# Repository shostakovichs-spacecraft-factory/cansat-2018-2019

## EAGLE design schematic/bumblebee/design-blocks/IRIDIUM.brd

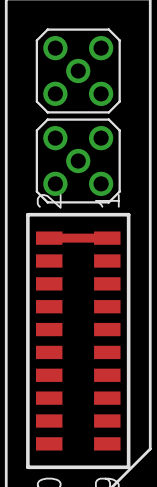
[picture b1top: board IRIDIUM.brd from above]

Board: 2 copper layers, 3 parts (0 on the bottom side), 2 nets.

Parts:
ANT: MMCX-P-P-X-ST-TH1
GPS: MMCX-P-P-X-ST-TH1
USER_PORT: SAMTEC-CLP-110-02-X-DJ; SAMTEC-CLP-110-02-X-D

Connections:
GND: ANT.2, ANT.3, ANT.4, ANT.5, GPS.2, GPS.3, GPS.4, GPS.5, USER_PORT.3, USER_PORT.4, USER_PORT.8, USER_PORT.15, USER_PORT.18
VCC5: USER_PORT.1, USER_PORT.2

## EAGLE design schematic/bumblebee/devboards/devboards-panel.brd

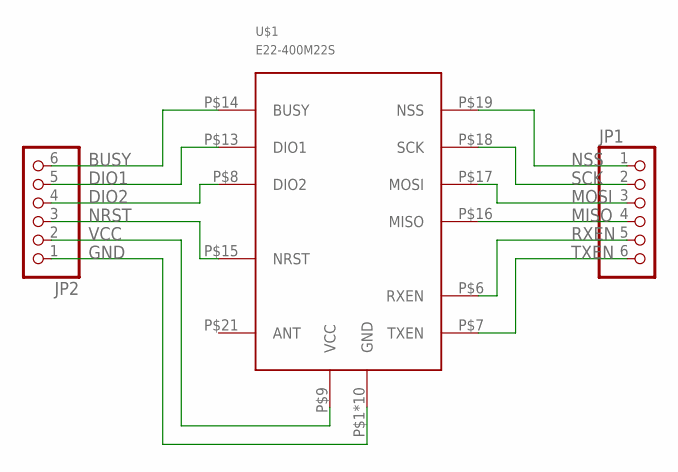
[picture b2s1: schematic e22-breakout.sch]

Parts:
JP1, JP2: PINHD-1X6; 1X06
U$1: E22-400M22S

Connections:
BUSY: JP2.6, U$1.P$14 (BUSY)
DIO1: JP2.5, U$1.P$13 (DIO1)
DIO2: JP2.4, U$1.P$8 (DIO2)
MISO: JP1.4, U$1.P$16 (MISO)
MOSI: JP1.3, U$1.P$17 (MOSI)
NRST: JP2.3, U$1.P$15 (NRST)
NSS: JP1.1, U$1.P$19 (NSS)
RXEN: JP1.5, U$1.P$6 (RXEN)
SCK: JP1.2, U$1.P$18 (SCK)
TXEN: JP1.6, U$1.P$7 (TXEN)
VCC: JP2.2, U$1.P$9 (VCC)

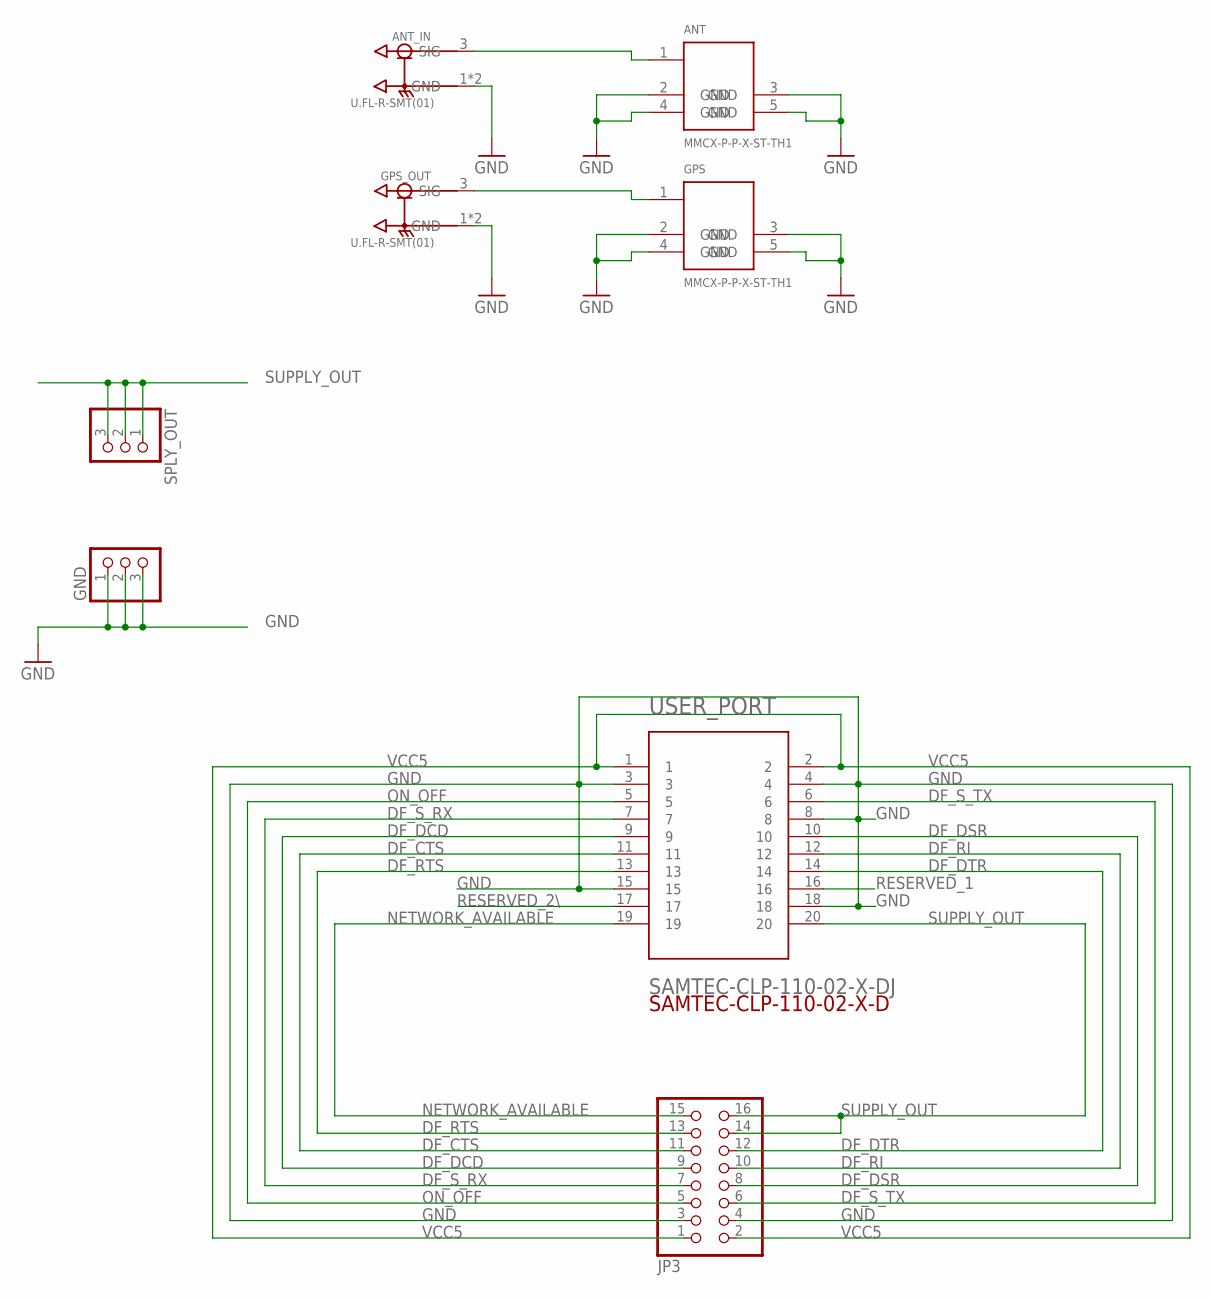
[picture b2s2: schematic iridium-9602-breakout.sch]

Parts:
ANT: MMCX-P-P-X-ST-TH1
ANT_IN: U.FL-R-SMT(01); HRS_U.FL-R-SMT(01)
GND: PINHD-1X3; 1X03
GPS: MMCX-P-P-X-ST-TH1
GPS_OUT: U.FL-R-SMT(01); HRS_U.FL-R-SMT(01)
JP3: PINHD-2X8; 2X08
SPLY_OUT: PINHD-1X3; 1X03
USER_PORT: SAMTEC-CLP-110-02-X-DJ; SAMTEC-CLP-110-02-X-D

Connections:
DF_CTS: JP3.11, USER_PORT.11
DF_DCD: JP3.9, USER_PORT.9
DF_DSR: JP3.8, USER_PORT.10
DF_DTR: JP3.12, USER_PORT.14
DF_RI: JP3.10, USER_PORT.12
DF_RTS: JP3.13, USER_PORT.13
DF_S_RX: JP3.7, USER_PORT.7
DF_S_TX: JP3.6, USER_PORT.6
GND: ANT.2 (GND), ANT.3 (GND), ANT.4 (GND), ANT.5 (GND), ANT_IN.1 (GND), ANT_IN.2 (GND), GND.1, GND.2, GND.3, GPS.2 (GND), GPS.3 (GND), GPS.4 (GND), GPS.5 (GND), GPS_OUT.1 (GND), GPS_OUT.2 (GND), JP3.3, JP3.4, USER_PORT.3, USER_PORT.4, USER_PORT.8, USER_PORT.15, USER_PORT.18
unnamed: ANT.1, ANT_IN.3 (SIG)
unnamed: GPS.1, GPS_OUT.3 (SIG)
NETWORK_AVAILABLE: JP3.15, USER_PORT.19
ON_OFF: JP3.5, USER_PORT.5
RESERVED_1: USER_PORT.16
RESERVED_2\: USER_PORT.17
SUPPLY_OUT: JP3.14, JP3.16, SPLY_OUT.1, SPLY_OUT.2, SPLY_OUT.3, USER_PORT.20
VCC5: JP3.1, JP3.2, USER_PORT.1, USER_PORT.2

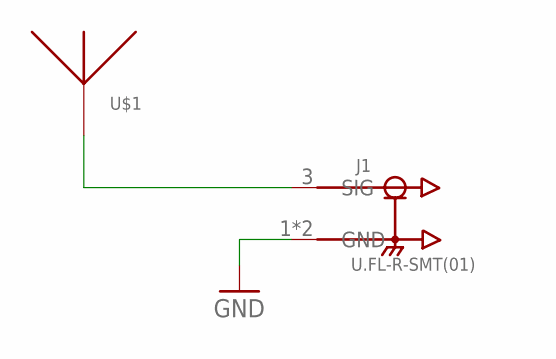
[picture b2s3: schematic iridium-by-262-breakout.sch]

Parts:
J1: U.FL-R-SMT(01); HRS_U.FL-R-SMT(01)
U$1: BY-IRIDIUM-254

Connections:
GND2: J1.1 (GND), J1.2 (GND)

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
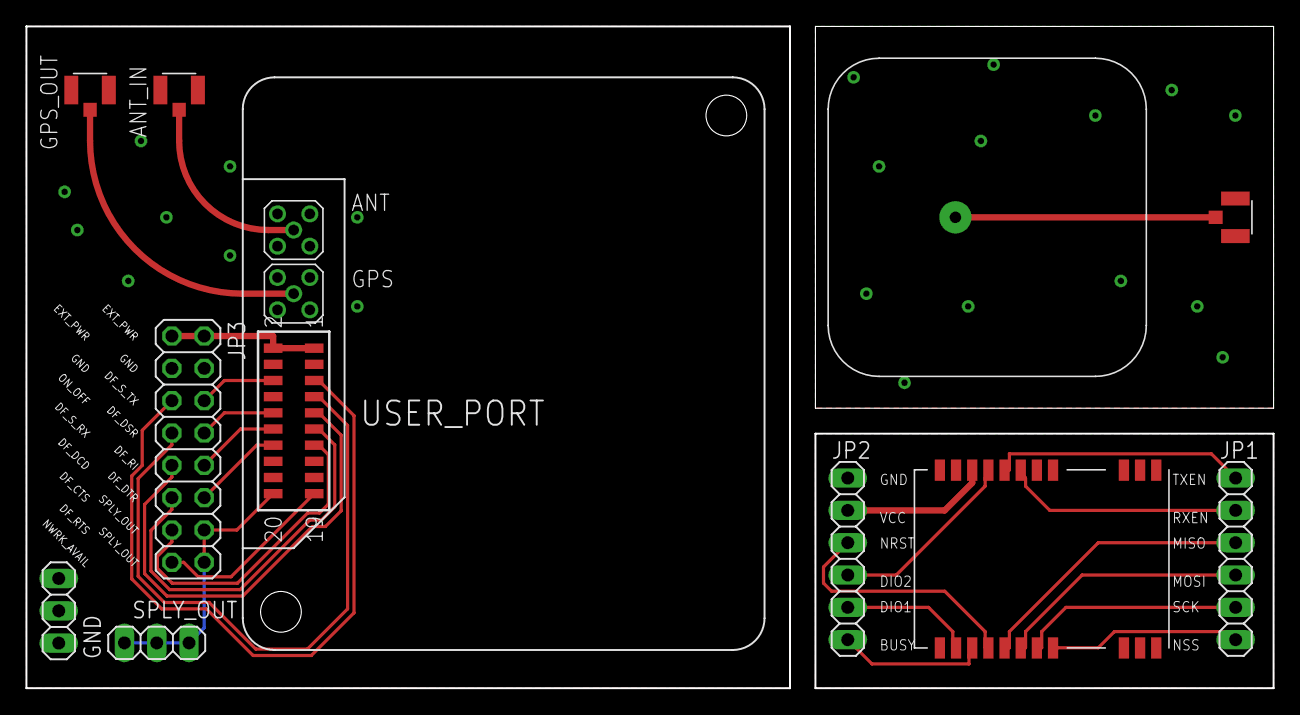
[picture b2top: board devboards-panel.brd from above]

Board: 2 copper layers, 98.0 x 52.0 mm, 13 parts (0 on the bottom side), 29 nets.

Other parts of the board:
U$2: BY-IRIDIUM-254

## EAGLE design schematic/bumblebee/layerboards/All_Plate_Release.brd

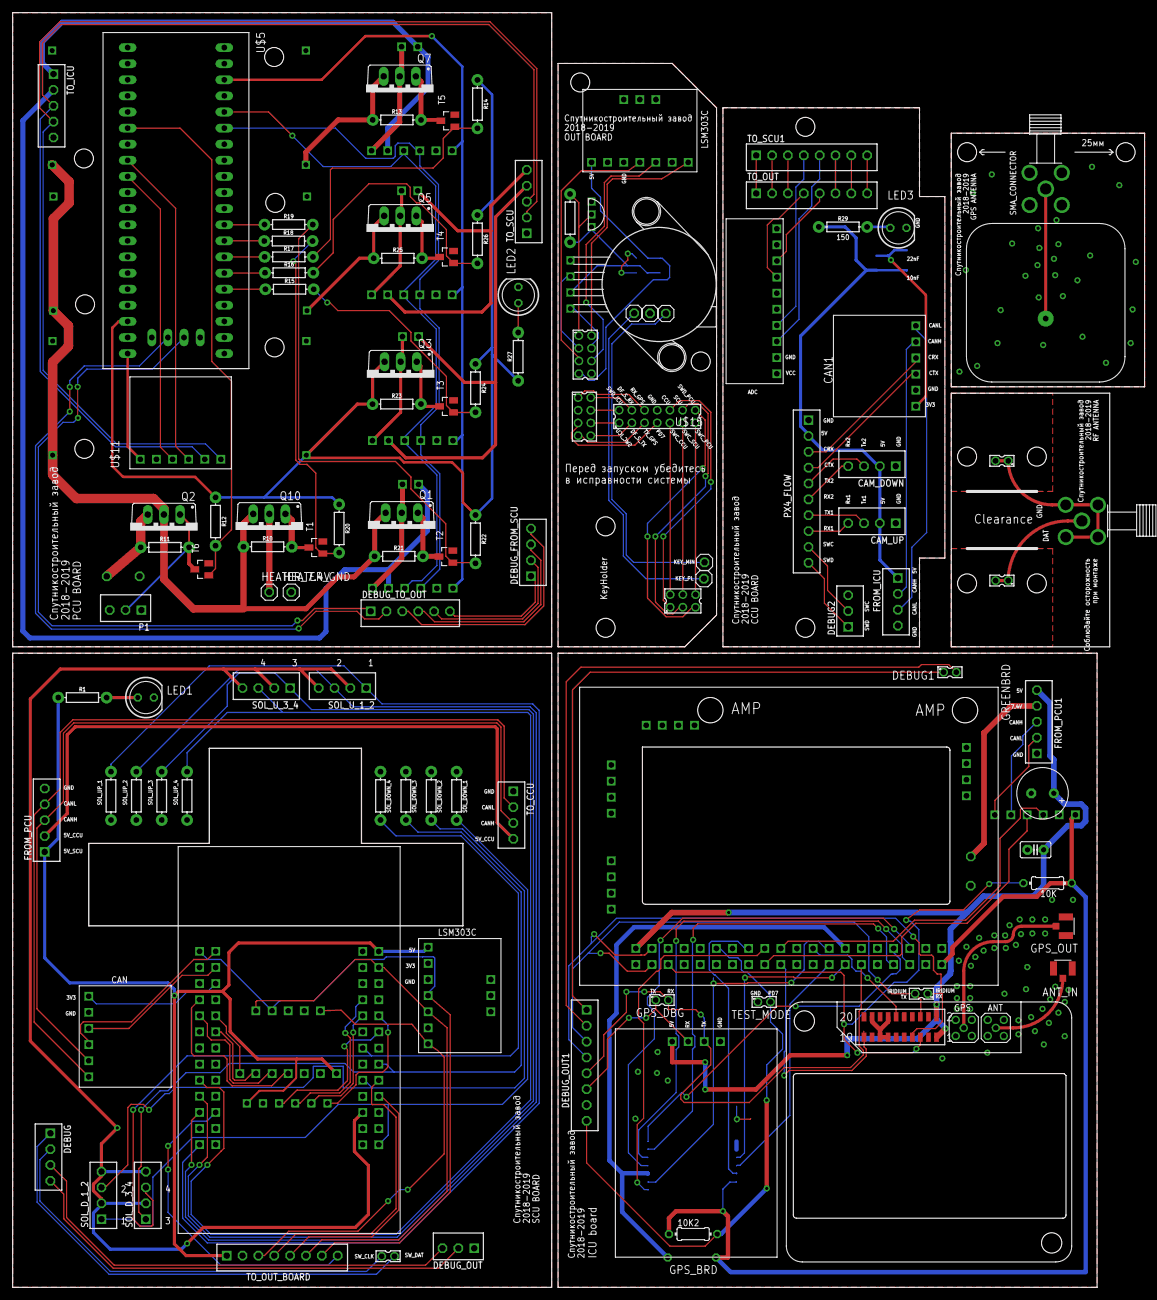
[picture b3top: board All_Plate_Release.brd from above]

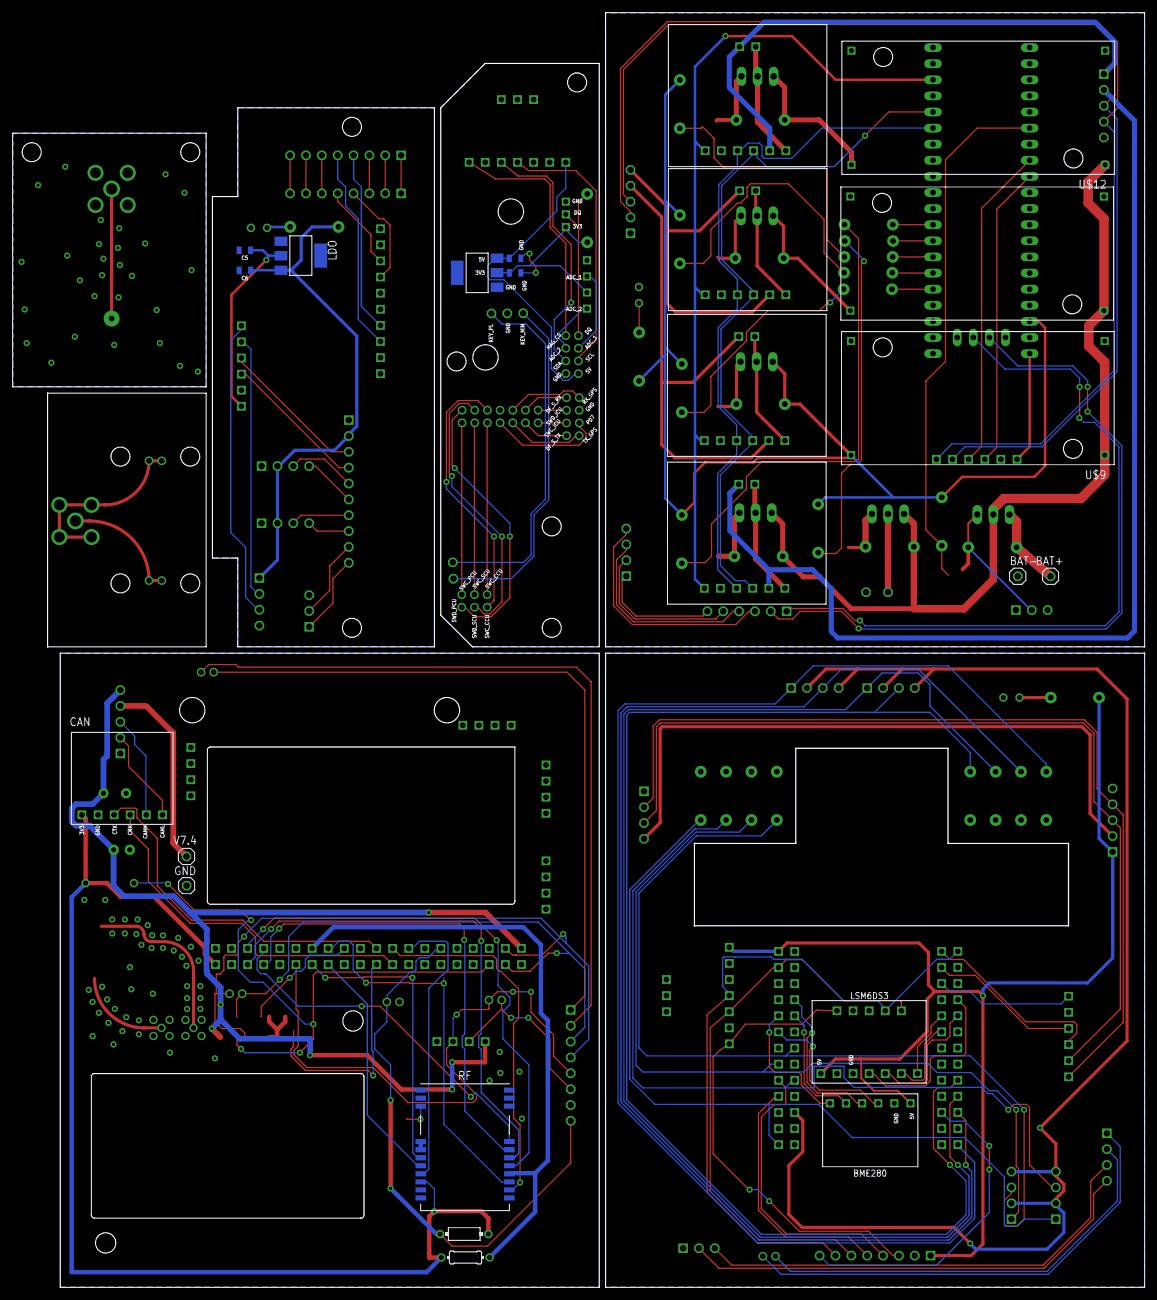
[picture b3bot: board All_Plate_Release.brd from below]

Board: 2 copper layers, 178.5 x 201.0 mm, 131 parts (22 on the bottom side), 164 nets.

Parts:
10K, 10K1, 10K2: 10K; 0204/7
ANT1: MMCX-P-P-X-ST-TH1
ANT_IN: U.FL-R-SMT(01); HRS_U.FL-R-SMT(01)
BAT+: 1X01
BAT-: 1X01
C1: E3,5-8
C2: C2.5-2
C3, C5: 22uF; 0805
C4, C6: 10uF; 0805
CAM_DOWN: B4B-EH-A
CAM_UP: B4B-EH-A
CAN, CAN1: CAN
DEBUG: B4B-EH-A
DEBUG1: 332-02
DEBUG2: B3B-EH-A
DEBUG_FROM_SCU: B4B-EH-A
DEBUG_OUT: B3B-EH-A
DEBUG_OUT1: B8B-EH-A
DEBUG_TO_OUT: B6B-EH-A
FROM_ICU: B4B-EH-A
FROM_PCU, FROM_PCU1: B5B-EH-A
GND: 1X01
GPS1: MMCX-P-P-X-ST-TH1
GPS_BRD: GPS
GPS_DBG: 332-02
GPS_OUT: U.FL-R-SMT(01); HRS_U.FL-R-SMT(01)
GREENBRD: ICU
HEATER_7.4V: 1X01
HEATER_GND: 1X01
IC1: REG1117; SOT223
IRIDIUM: 332-02
J1: 221790-1; TE_221790-1
JP1, JP2, JP6, JP7, JP8: 1X01
LDO: REG1117; SOT223
LED1, LED2, LED3: LED5MM
P1: B3B-EH-A
PX4_FLOW: B10B-EH-A
Q1, Q2, Q3, Q5, Q7, Q10: IRF9530; TO220BV
R1, R2, R3, R4, R5, R6, R7, R8, R9, R27, R29: 150; AXIAL-0.3
R10, R11, R12, R13, R14, R20, R21, R22, R23, R24, R25, R26: 10k; AXIAL-0.3
R15, R16, R17, R18, R19: 10; AXIAL-0.3
R28: 4k7; AXIAL-0.3
RF: E22-400M22S
SMA_CONNECTOR: 221790-1; TE_221790-1
SOL_D_1_2, SOL_D_3_4: B4B-EH-A
SOL_U_1_2, SOL_U_3_4: B4B-EH-A
T1, T2, T3, T4, T5, T6: 2N7002E; SOT23
TEST_MODE: 332-02
TO_CCU: B4B-EH-A
TO_ICU: B5B-EH-A
TO_OUT: B8B-EH-A
TO_OUT_BOARD: B8B-EH-A
TO_SCU: B5B-EH-A
TO_SCU1: B8B-EH-A
U$1: SCU
U$2: BME
U$3: LSM6DS3
U$4, U$17: LSM303C
U$5: BLUEPILLTHEONLYONE; BLUEPIL
U$6, U$8, U$13, U$14: INA
U$7, U$11: CAN
U$9, U$10, U$12: DCDC
U$15: MPX
U$16: TEMP
U$18: ADS
U$19: BY-IRIDIUM-254
USER_PORT1: SAMTEC-CLP-110-02-X-DJ; SAMTEC-CLP-110-02-X-D
V7.4: 1X01
X1, X6, X7: 332-02
X2: 332-14
X3, X4: 332-08
X5: 332-06

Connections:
3.3V: 10K.1, 10K1.1, 10K2.1, CAN.3V3, GREENBRD.3V3_0, RF.P$9
3V1: U$5.3V3_0, U$5.3V3_1, U$5.3V3_2, U$6.VCC, U$8.VCC, U$11.3V3, U$13.VCC, U$14.VCC
3V2: C3.1, IC1.2, R28.P$1, U$15.VCC, U$16.VDD
3V3: SOL_D_1_2.2, SOL_D_1_2.4, SOL_D_3_4.2, SOL_D_3_4.4, SOL_U_1_2.2, SOL_U_1_2.4, SOL_U_3_4.2, SOL_U_3_4.4, U$1.3.3V
3V4: C5.1, CAN1.3V3, LDO.2
5V: C4.1, IC1.3, U$17.5V, X3.7
5V_CCU: FROM_PCU.2, TO_CCU.4
5V_CCU1: TO_SCU.4, U$14.VIN-_0, U$14.VIN-_1
5V_CCU2: C6.1, CAM_DOWN.2, CAM_UP.2, FROM_ICU.1, LDO.3, PX4_FLOW.2, R29.P$1
5V_CONTINUOUS: Q3.S, R12.P$1, R14.P$1, R20.P$1, R22.P$1, R23.P$1, R24.P$1, R26.P$1, R27.P$1, U$5.5V, U$9.OUT+
5V_ICU: C1.+, C2.2, FROM_PCU1.5, GPS_BRD.UCC, GREENBRD.5V_0, USER_PORT1.1, USER_PORT1.2
5V_ICU1: TO_ICU.1, U$6.VIN-_0, U$6.VIN-_1
5V_SCU: FROM_PCU.1, R1.P$1, TO_OUT_BOARD.1, U$1.VIN, U$2.VCC, U$3.VIN, U$4.5V
5V_SCU1: TO_SCU.5, U$13.VIN-_0, U$13.VIN-_1
7.4V: FROM_PCU1.4, V7.4.1
7.4V1: TO_ICU.2, U$8.VIN-_0, U$8.VIN-_1
ADC_1: U$15.V1, X3.3
ADC_2: U$15.V2, X3.4
ADC_OUT_1: TO_OUT_BOARD.5, U$1.PA1
ADC_OUT_2: TO_OUT_BOARD.4, U$1.PA3
CANH: TO_ICU.3, TO_SCU.3, U$11.CANH
CANL: TO_ICU.4, TO_SCU.2, U$11.CANL
CRX: CAN1.CRX, PX4_FLOW.3
CTX: CAN1.CTX, PX4_FLOW.4
DAT: J1.1, X6.1, X6.2
DF_RI: GREENBRD.PC9, USER_PORT1.12
DF_S_RX: DEBUG_OUT1.4, GREENBRD.PB7, IRIDIUM.1, USER_PORT1.7
DF_S_RX1: X2.4, X4.2
DF_S_TX: DEBUG_OUT1.3, GREENBRD.PB6, IRIDIUM.2, USER_PORT1.6
DF_S_TX1: X2.3, X4.8
DQ: R28.P$2, U$16.DQ, X3.1
DQ_TEMP: TO_OUT_BOARD.8, U$1.PB0
GND: FROM_PCU.5, LED1.K, R2.P$1, R3.P$1, R4.P$2, R5.P$1, R6.P$1, R7.P$2, R8.P$2, R9.P$1, TO_CCU.1, TO_OUT_BOARD.2, U$1.GND_2, U$2.GND, U$3.GND, U$4.GND, U$7.GND
GND1: ANT1.2, ANT1.3, ANT1.4, ANT1.5, ANT_IN.1, ANT_IN.2, C1.-, C2.1, CAN.GND, DEBUG_OUT1.7, FROM_PCU1.1, GND.1, GPS1.2, GPS1.3, GPS1.4, GPS1.5, GPS_BRD.GND, GPS_OUT.1, GPS_OUT.2, GREENBRD.GND_0, GREENBRD.GND_1, RF.P$1, RF.P$2, RF.P$3, RF.P$4, RF.P$5, RF.P$10, RF.P$11, RF.P$12, RF.P$20, RF.P$22, TEST_MODE.1, USER_PORT1.3, USER_PORT1.4, USER_PORT1.8, USER_PORT1.13, USER_PORT1.14, USER_PORT1.15, USER_PORT1.18
GND2: BAT-.1, HEATER_GND.1, LED2.K, P1.1, P1.3, T1.2, T2.2, T3.2, T4.2, T5.2, T6.2, TO_ICU.5, TO_SCU.1, U$5.GND0, U$5.GND1, U$5.GND2, U$5.GND3, U$6.GND, U$8.GND, U$9.IN-, U$9.OUT-, U$10.IN-, U$10.OUT-, U$11.GND, U$12.IN-, U$12.OUT-, U$13.GND, U$14.GND
GND3: C3.2, C4.2, IC1.1, JP7.1, U$15.GND, U$16.GND, U$17.GND, X2.8, X3.8, X4.3
GND4: C5.2, C6.2, CAM_DOWN.1, CAM_UP.1, CAN1.GND, FROM_ICU.4, LDO.1, LED3.K, PX4_FLOW.1
GND5: J1.2, J1.3, J1.4, J1.5, X7.1, X7.2
GND6: SMA_CONNECTOR.2, SMA_CONNECTOR.3, SMA_CONNECTOR.4, SMA_CONNECTOR.5
HEATER_7.4V: HEATER_7.4V.1, Q10.D
KEY_1: BAT+.1, Q2.S, R11.P$1
KEY_2: Q1.S, Q2.D, Q10.S, R10.P$1, R21.P$1, U$9.IN+, U$10.IN+, U$12.IN+
KEY_MINUS: JP1.1, JP6.1
KEY_PLUS: JP2.1, JP8.1
KILLSWITCH: R12.P$2, T6.1, U$5.A9
MAG_CS: TO_OUT_BOARD.3, U$3.OCS, U$4.CSM
MAG_CS1: U$17.CSM, X3.2
MISO_2: U$1.PB14, U$2.SDO
MISO_3: U$1.PC11, U$3.SAD
MOSI_2: U$1.PB15, U$2.SDA
MOSI_3: U$1.PC12, U$3.SDA
unnamed: GREENBRD.PB14, RF.P$16
unnamed: GREENBRD.PB12, RF.P$19
unnamed: GREENBRD.PE15, RF.P$6
unnamed: ANT1.1, ANT_IN.3
unnamed: GPS1.1, GPS_OUT.3
unnamed: U$1.PA11, U$7.CRX
unnamed: U$1.PA12, U$7.CTX
unnamed: GREENBRD.PB13, RF.P$18
unnamed: CAN.CANL, FROM_PCU1.2
unnamed: CAN.CTX, GREENBRD.PD1
unnamed: CAN.CANH, FROM_PCU1.3
unnamed: GREENBRD.PD15, RF.P$13
unnamed: GREENBRD.PD13, RF.P$8
unnamed: CAN.CRX, GREENBRD.PD0
unnamed: GREENBRD.PB15, RF.P$17
unnamed: U$1.+3.3V, U$7.3V3
unnamed: GREENBRD.PE12, RF.P$14
unnamed: 10K1.2, GREENBRD.PE14, RF.P$15
unnamed: LED1.A, R1.P$2
unnamed: FROM_PCU.3, TO_CCU.3, U$7.CANH
unnamed: FROM_PCU.4, TO_CCU.2, U$7.CANL
unnamed: DEBUG.3, DEBUG_OUT.3
unnamed: DEBUG.4, DEBUG_OUT.2
unnamed: GREENBRD.PE13, RF.P$7
unnamed: Q1.G, R21.P$2, T2.3
unnamed: Q3.G, R23.P$2, T3.3
unnamed: Q5.G, R25.P$2, T4.3
unnamed: Q5.S, R25.P$1, U$10.OUT+
unnamed: Q7.G, R13.P$2, T5.3
unnamed: Q7.S, R13.P$1, U$12.OUT+
unnamed: Q3.D, U$14.VIN+_0, U$14.VIN+_1
unnamed: Q5.D, U$13.VIN+_0, U$13.VIN+_1
unnamed: Q7.D, U$6.VIN+_0, U$6.VIN+_1
unnamed: Q1.D, U$8.VIN+_0, U$8.VIN+_1
unnamed: U$5.B10, U$6.SCL, U$8.SCL, U$13.SCL, U$14.SCL
unnamed: U$5.B11, U$6.SDA, U$8.SDA, U$13.SDA, U$14.SDA
unnamed: U$5.A12, U$11.CTX
unnamed: U$5.A11, U$11.CRX
unnamed: LED2.A, R27.P$2
unnamed: Q10.G, R10.P$2, T1.3
unnamed: R15.P$1, U$5.A0
unnamed: R16.P$1, U$5.A1
unnamed: R17.P$1, U$5.A2
unnamed: R18.P$1, U$5.A3
unnamed: R19.P$1, U$5.A4
unnamed: P1.2, Q2.G, R11.P$2, T6.3
unnamed: CAN1.CANL, FROM_ICU.3
unnamed: CAN1.CANH, FROM_ICU.2
unnamed: LED3.A, R29.P$2
unnamed: TO_OUT.8, TO_SCU1.8
unnamed: TO_OUT.7, TO_SCU1.7
unnamed: TO_OUT.6, TO_SCU1.6
unnamed: TO_OUT.3, TO_SCU1.3
unnamed: TO_OUT.2, TO_SCU1.2
unnamed: TO_OUT.1, TO_SCU1.1
unnamed: TO_SCU1.5, U$18.SCL
unnamed: TO_SCU1.4, U$18.SDA
unnamed: TO_OUT.5, U$18.A1
unnamed: TO_OUT.4, U$18.A0
unnamed: SMA_CONNECTOR.1, U$19.P$1
NETWORK_AVAILABLE: GREENBRD.PE7, USER_PORT1.19
NSS_2: U$1.PB12, U$2.CSB
NSS_3: U$1.PD2, U$3.CS
ON_OFF: 10K.2, GREENBRD.PB4, USER_PORT1.5
PCTRL_AMP: R19.P$2, R22.P$2, T2.1
PCTRL_CCU: R15.P$2, R24.P$2, T3.1
PCTRL_HEATER: R18.P$2, R20.P$2, T1.1
PCTRL_ICU: R14.P$2, R17.P$2, T5.1
PCTRL_SCU: R16.P$2, R26.P$2, T4.1
PD1: X2.7, X4.5
PD7: 10K2.2, DEBUG_OUT1.8, GREENBRD.PD7, TEST_MODE.2
RX1: CAM_UP.4, PX4_FLOW.8
RX2: CAM_DOWN.4, PX4_FLOW.6
RX_GPS: DEBUG_OUT1.6, GPS_BRD.RX, GPS_DBG.1
RX_GPS1: X2.6, X4.1
SCK_2: U$1.PB13, U$2.SCL
SCK_3: U$1.PC10, U$3.SCL
SCL: U$17.SCL, X3.5
SCL3: TO_OUT_BOARD.7, U$1.PA8, U$3.SCX, U$4.SCL
SDA: U$17.SDA, X3.6
SDA3: TO_OUT_BOARD.6, U$1.PC9, U$3.SDX, U$4.SDA
SOL_D_1: R9.P$2, SOL_D_1_2.1, U$1.PC2
SOL_D_2: R8.P$1, SOL_D_1_2.3, U$1.PC3
SOL_D_3: R7.P$1, SOL_D_3_4.1, U$1.PC4
SOL_D_4: R6.P$2, SOL_D_3_4.3, U$1.PC5
SOL_U_1: R5.P$2, SOL_U_1_2.1, U$1.PB1
SOL_U_2: R4.P$1, SOL_U_1_2.3, U$1.PA7
SOL_U_3: R3.P$2, SOL_U_3_4.1, U$1.PC1
SOL_U_4: R2.P$2, SOL_U_3_4.3, U$1.PA5
SWC: DEBUG1.2, DEBUG_OUT1.2
SWC1: DEBUG2.2, PX4_FLOW.9
SWCLK_0: DEBUG_TO_OUT.1, U$5.SWCLK
SWCLK_2: DEBUG_FROM_SCU.3, DEBUG_TO_OUT.4
SWCLK_3: DEBUG_FROM_SCU.1, DEBUG_TO_OUT.6
SWCLK_CCU: X2.9, X5.2
SWCLK_PCU: X2.13, X5.6
SWCLK_SCU: X2.11, X5.4
SWC_ICU: X2.1, X4.6
SWD: DEBUG1.1, DEBUG_OUT1.1
SWD1: DEBUG2.1, PX4_FLOW.10
SWDIO_0: DEBUG_TO_OUT.2, U$5.SWDIO
SWDIO_2: DEBUG_FROM_SCU.4, DEBUG_TO_OUT.3
SWDIO_3: DEBUG_FROM_SCU.2, DEBUG_TO_OUT.5
SWDIO_CCU: X2.10, X5.1
SWDIO_PCU: X2.14, X5.5
SWDIO_SCU: X2.12, X5.3
SWD_ICU: X2.2, X4.4
SW_CLK: DEBUG.2, X1.2
SW_DAT: DEBUG.1, X1.1
TX1: CAM_UP.3, PX4_FLOW.7
TX2: CAM_DOWN.3, PX4_FLOW.5
TX_GPS: DEBUG_OUT1.5, GPS_BRD.TX, GPS_DBG.2, GREENBRD.PD9
TX_GPS1: X2.5, X4.7

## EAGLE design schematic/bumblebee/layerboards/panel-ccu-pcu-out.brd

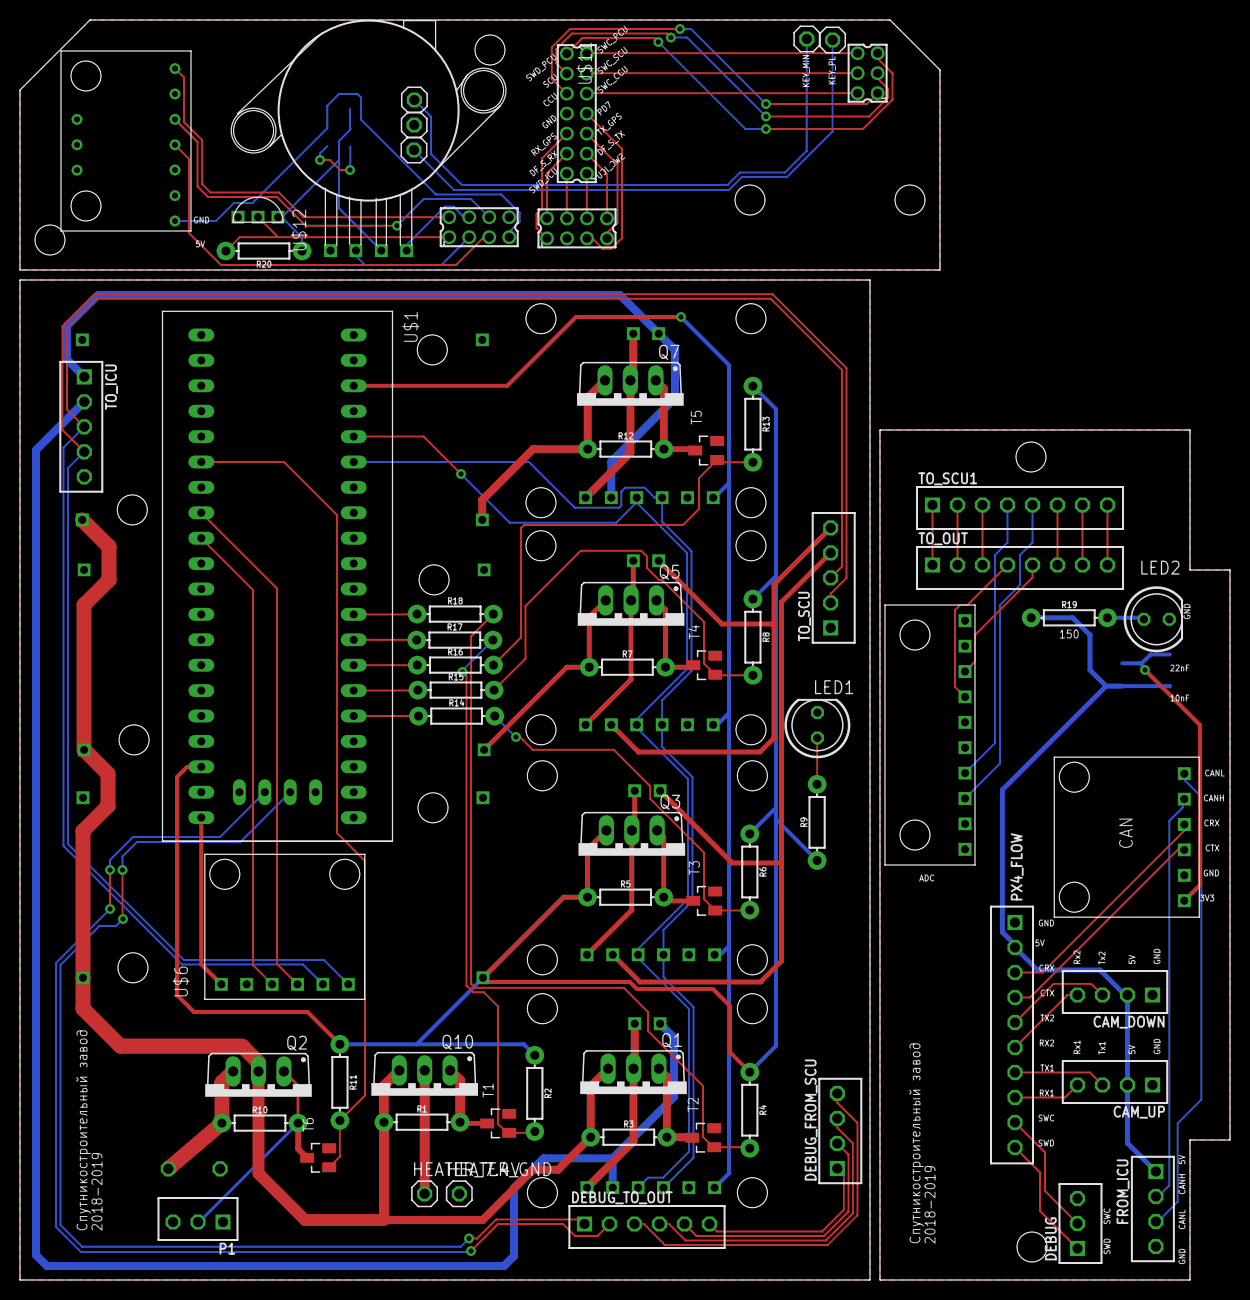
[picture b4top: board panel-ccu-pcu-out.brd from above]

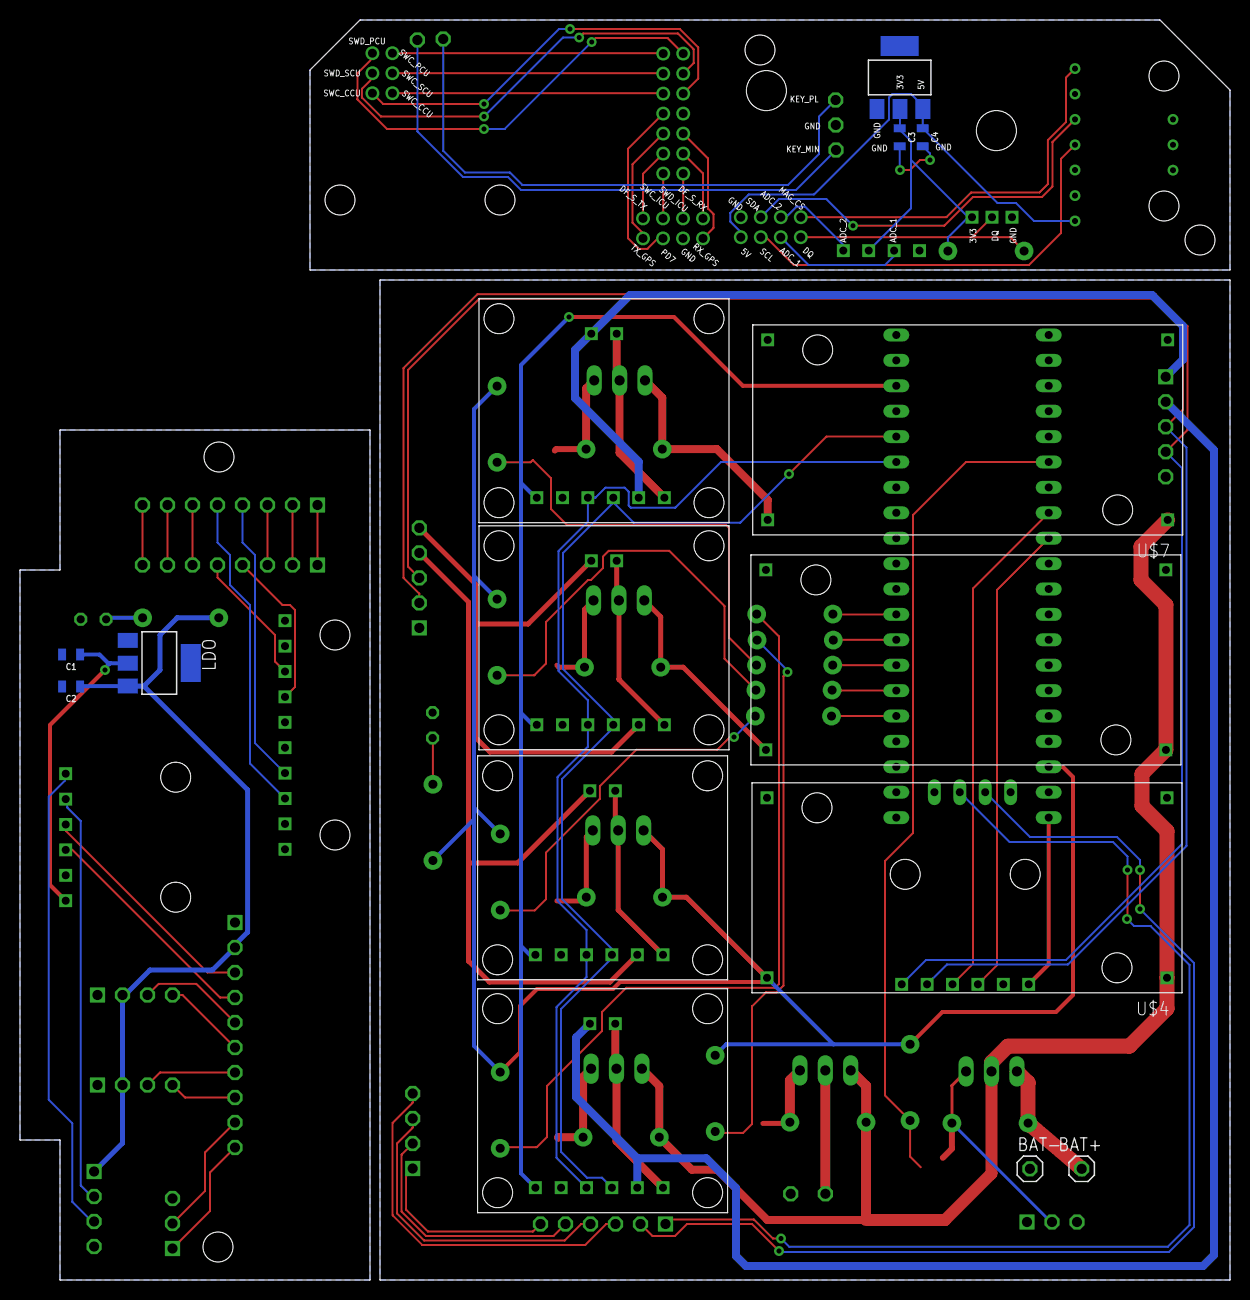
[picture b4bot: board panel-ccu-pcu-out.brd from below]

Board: 2 copper layers, 121.0 x 126.0 mm, 79 parts (15 on the bottom side), 94 nets.

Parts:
BAT+: 1X01
BAT-: 1X01
C1, C3: 22uF; 0805
C2, C4: 10uF; 0805
CAM_DOWN: B4B-EH-A
CAM_UP: B4B-EH-A
CAN: CAN
DEBUG: B3B-EH-A
DEBUG_FROM_SCU: B4B-EH-A
DEBUG_TO_OUT: B6B-EH-A
FROM_ICU: B4B-EH-A
HEATER_7.4V: 1X01
HEATER_GND: 1X01
IC1: REG1117; SOT223
JP1, JP2, JP6, JP7, JP8: 1X01
LDO: REG1117; SOT223
LED1, LED2: LED5MM
P1: B3B-EH-A
PX4_FLOW: B10B-EH-A
Q1, Q2, Q3, Q5, Q7, Q10: IRF9530; TO220BV
R1, R2, R3, R4, R5, R6, R7, R8, R10, R11, R12, R13: 10k; AXIAL-0.3
R9, R19: 150; AXIAL-0.3
R14, R15, R16, R17, R18: 10; AXIAL-0.3
R20: 4k7; AXIAL-0.3
T1, T2, T3, T4, T5, T6: 2N7002E; SOT23
TO_ICU: B5B-EH-A
TO_OUT: B8B-EH-A
TO_SCU: B5B-EH-A
TO_SCU1: B8B-EH-A
U$1: BLUEPILLTHEONLYONE; BLUEPIL
U$2, U$3, U$8, U$9: INA
U$4, U$5, U$7: DCDC
U$6: CAN
U$10: ADS
U$11: MPX
U$12: TEMP
U$13: LSM303C
X1: 332-14
X2, X3: 332-08
X4: 332-06

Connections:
3V1: C1.1, CAN.3V3, LDO.2
3V2: C3.1, IC1.2, R20.P$1, U$11.VCC, U$12.VDD
3V3: U$1.3V3_0, U$1.3V3_1, U$1.3V3_2, U$2.VCC, U$3.VCC, U$6.3V3, U$8.VCC, U$9.VCC
5V: C4.1, IC1.3, U$13.5V, X2.7
5V_CCU: TO_SCU.4, U$9.VIN-_0, U$9.VIN-_1
5V_CCU1: C2.1, CAM_DOWN.2, CAM_UP.2, FROM_ICU.1, LDO.3, PX4_FLOW.2, R19.P$1
5V_CONTINUOUS: Q3.S, R2.P$1, R4.P$1, R5.P$1, R6.P$1, R8.P$1, R9.P$1, R11.P$1, R13.P$1, U$1.5V, U$4.OUT+
5V_ICU: TO_ICU.1, U$2.VIN-_0, U$2.VIN-_1
5V_SCU: TO_SCU.5, U$8.VIN-_0, U$8.VIN-_1
7.4V: TO_ICU.2, U$3.VIN-_0, U$3.VIN-_1
ADC_1: U$11.V1, X2.3
ADC_2: U$11.V2, X2.4
CANH: TO_ICU.3, TO_SCU.3, U$6.CANH
CANL: TO_ICU.4, TO_SCU.2, U$6.CANL
CRX: CAN.CRX, PX4_FLOW.3
CTX: CAN.CTX, PX4_FLOW.4
DF_S_RX: X1.4, X3.2
DF_S_TX: X1.3, X3.8
DQ: R20.P$2, U$12.DQ, X2.1
GND: BAT-.1, HEATER_GND.1, LED1.K, P1.1, P1.3, T1.2, T2.2, T3.2, T4.2, T5.2, T6.2, TO_ICU.5, TO_SCU.1, U$1.GND0, U$1.GND1, U$1.GND2, U$1.GND3, U$2.GND, U$3.GND, U$4.IN-, U$4.OUT-, U$5.IN-, U$5.OUT-, U$6.GND, U$7.IN-, U$7.OUT-, U$8.GND, U$9.GND
GND1: C1.2, C2.2, CAM_DOWN.1, CAM_UP.1, CAN.GND, FROM_ICU.4, LDO.1, LED2.K, PX4_FLOW.1
GND2: C3.2, C4.2, IC1.1, JP7.1, U$11.GND, U$12.GND, U$13.GND, X1.8, X2.8, X3.3
HEATER_7.4V: HEATER_7.4V.1, Q10.D
KEY_1: BAT+.1, Q2.S, R10.P$1
KEY_2: Q1.S, Q2.D, Q10.S, R1.P$1, R3.P$1, U$4.IN+, U$5.IN+, U$7.IN+
KEY_MINUS: JP1.1, JP6.1
KEY_PLUS: JP2.1, JP8.1
KILLSWITCH: R11.P$2, T6.1, U$1.A9
MAG_CS: U$13.CSM, X2.2
unnamed: Q1.G, R3.P$2, T2.3
unnamed: U$1.A11, U$6.CRX
unnamed: Q5.G, R7.P$2, T4.3
unnamed: Q7.G, R12.P$2, T5.3
unnamed: Q5.S, R7.P$1, U$5.OUT+
unnamed: Q3.G, R5.P$2, T3.3
unnamed: Q7.S, R12.P$1, U$7.OUT+
unnamed: Q1.D, U$3.VIN+_0, U$3.VIN+_1
unnamed: Q3.D, U$9.VIN+_0, U$9.VIN+_1
unnamed: Q5.D, U$8.VIN+_0, U$8.VIN+_1
unnamed: Q7.D, U$2.VIN+_0, U$2.VIN+_1
unnamed: U$1.B11, U$2.SDA, U$3.SDA, U$8.SDA, U$9.SDA
unnamed: U$1.B10, U$2.SCL, U$3.SCL, U$8.SCL, U$9.SCL
unnamed: U$1.A12, U$6.CTX
unnamed: LED1.A, R9.P$2
unnamed: Q10.G, R1.P$2, T1.3
unnamed: R14.P$1, U$1.A0
unnamed: R15.P$1, U$1.A1
unnamed: R16.P$1, U$1.A2
unnamed: R17.P$1, U$1.A3
unnamed: R18.P$1, U$1.A4
unnamed: P1.2, Q2.G, R10.P$2, T6.3
unnamed: CAN.CANL, FROM_ICU.3
unnamed: CAN.CANH, FROM_ICU.2
unnamed: LED2.A, R19.P$2
unnamed: TO_OUT.8, TO_SCU1.8
unnamed: TO_OUT.7, TO_SCU1.7
unnamed: TO_OUT.6, TO_SCU1.6
unnamed: TO_OUT.3, TO_SCU1.3
unnamed: TO_OUT.2, TO_SCU1.2
unnamed: TO_OUT.1, TO_SCU1.1
unnamed: TO_SCU1.5, U$10.SCL
unnamed: TO_SCU1.4, U$10.SDA
unnamed: TO_OUT.5, U$10.A1
unnamed: TO_OUT.4, U$10.A0
PCTRL_AMP: R4.P$2, R18.P$2, T2.1
PCTRL_CCU: R6.P$2, R14.P$2, T3.1
PCTRL_HEATER: R2.P$2, R17.P$2, T1.1
PCTRL_ICU: R13.P$2, R16.P$2, T5.1
PCTRL_SCU: R8.P$2, R15.P$2, T4.1
PD7: X1.7, X3.5
RX1: CAM_UP.4, PX4_FLOW.8
RX2: CAM_DOWN.4, PX4_FLOW.6
RX_GPS: X1.6, X3.1
SCL: U$13.SCL, X2.5
SDA: U$13.SDA, X2.6
SWC: DEBUG.2, PX4_FLOW.9
SWCLK_0: DEBUG_TO_OUT.1, U$1.SWCLK
SWCLK_2: DEBUG_FROM_SCU.3, DEBUG_TO_OUT.4
SWCLK_3: DEBUG_FROM_SCU.1, DEBUG_TO_OUT.6
SWCLK_CCU: X1.9, X4.2
SWCLK_PCU: X1.13, X4.6
SWCLK_SCU: X1.11, X4.4
SWC_ICU: X1.1, X3.6
SWD: DEBUG.1, PX4_FLOW.10
SWDIO_0: DEBUG_TO_OUT.2, U$1.SWDIO
SWDIO_2: DEBUG_FROM_SCU.4, DEBUG_TO_OUT.3
SWDIO_3: DEBUG_FROM_SCU.2, DEBUG_TO_OUT.5
SWDIO_CCU: X1.10, X4.1
SWDIO_PCU: X1.14, X4.5
SWDIO_SCU: X1.12, X4.3
SWD_ICU: X1.2, X3.4
TX1: CAM_UP.3, PX4_FLOW.7
TX2: CAM_DOWN.3, PX4_FLOW.5
TX_GPS: X1.5, X3.7

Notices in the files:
parts and their libraries:
con-jst-eh: Copyright (C) 2016, Bob Starr
SparkFun-Resistors: Licensing: Creative Commons ShareAlike 4.0 International - https://creativecommons.org/licenses/by-sa/4.0
